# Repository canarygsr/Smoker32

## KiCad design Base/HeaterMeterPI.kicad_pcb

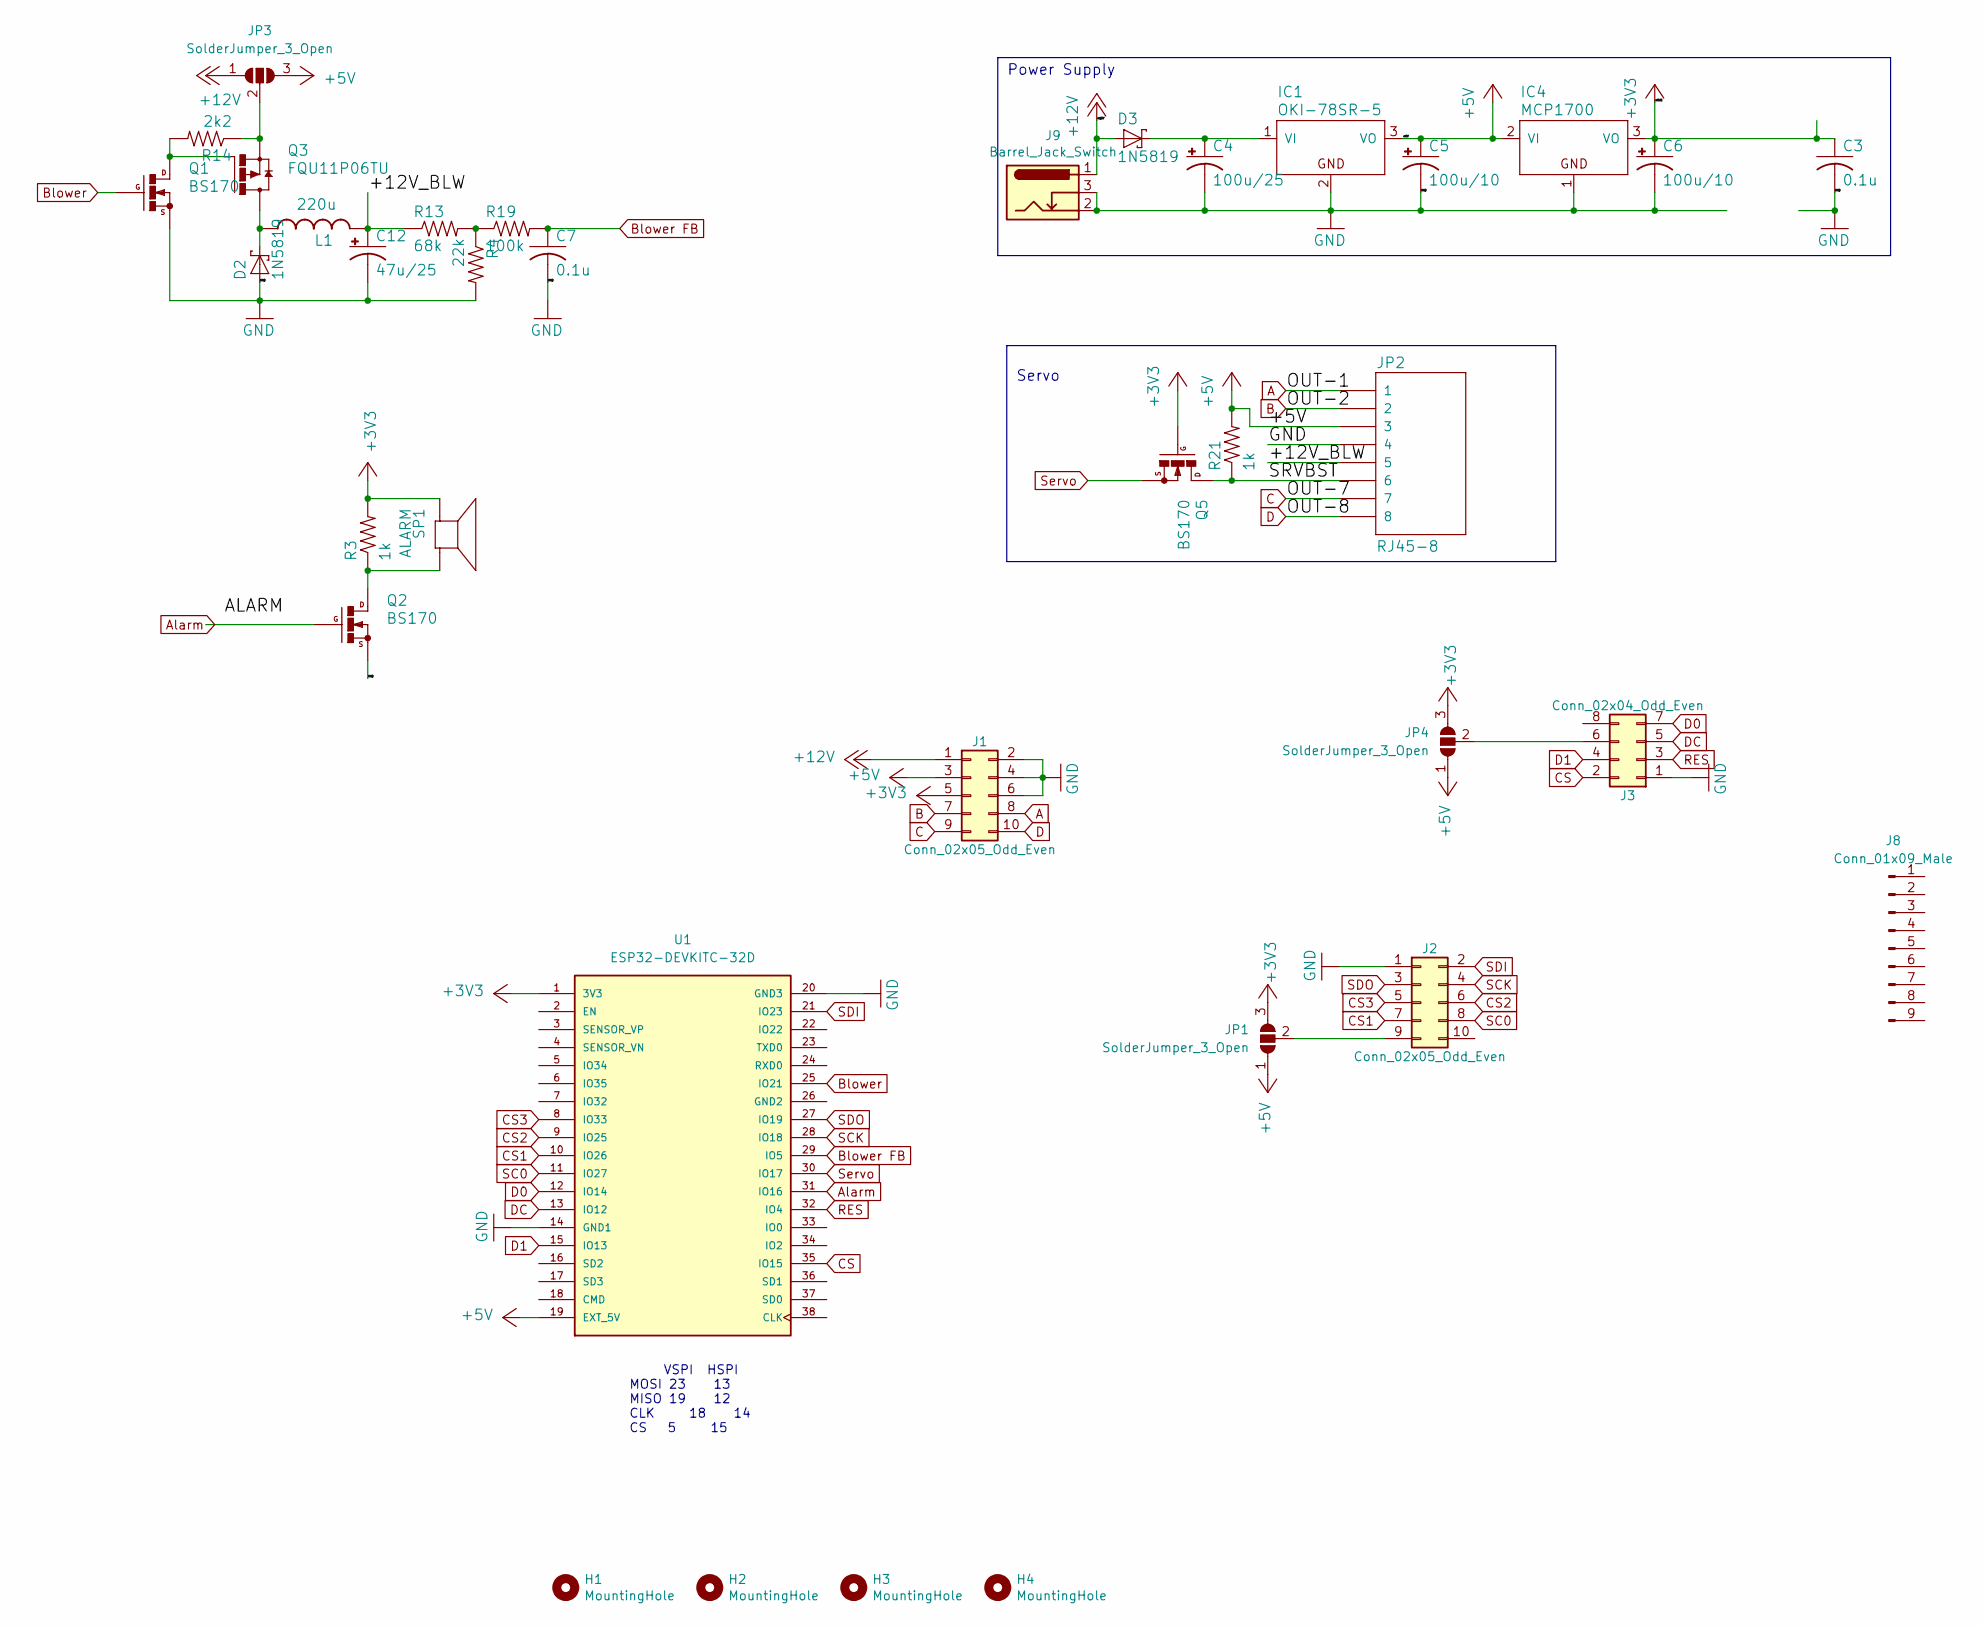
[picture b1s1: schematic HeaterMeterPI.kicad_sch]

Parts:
C3, C7: 0.1u; C025-025X050
C4: 100u/25; E2,5-6
C5, C6: 100u/10; E2,5-5
C12: 47u/25; E2,5-5
D2, D3: 1N5819; DO41-7
H1, H2, H3, H4: MountingHole; MountingHole_2.1mm
IC1: OKI-78SR-5; TO220HMURATA
IC4: MCP1700; TO92
J1: Conn_02x05_Odd_Even; PinHeader_2x06_P2.54mm_Vertical
J2: Conn_02x05_Odd_Even; PinHeader_1x09_P2.54mm_Vertical
J3: Conn_02x04_Odd_Even; PinHeader_1x07_P2.54mm_Vertical
J8: Conn_01x09_Male; Quad Max3186
J9: Barrel_Jack_Switch; BarrelJack_Horizontal
JP1, JP3, JP4: SolderJumper_3_Open; SolderJumper-3_P1.3mm_Open_RoundedPad1.0x1.5mm_NumberLabels
JP2: RJ45-8; RJ45-8-1H
L1: 220u; E5-9
Q1, Q2, Q5: BS170; SOT54E
Q3: FQU11P06TU; TO251
R3, R21: 1k; 0204_7
R4: 22k; 0204_7
R13: 68k; 0204_7
R14: 2k2; 0204_7
R19: 100k; 0204_7
SP1: ALARM; AL11P
U1: ESP32-DEVKITC-32D; MODULE_ESP32-NodeMCU; PARTREV 4

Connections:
+3V3: C3.1, C6.+, IC4.3 (VO), J1.5, JP1.3 (B), JP4.3 (B), Q5.G, R3.2, SP1.+, U1.1 (3V3)
+5V: C5.+, IC1.3 (VO), IC4.2 (VI), J1.3, JP1.1 (A), JP2.3, JP3.3 (B), JP4.1 (A), R21.2, U1.19 (EXT_5V)
+12V: D3.A, J1.1, J9.1, JP3.1 (A)
/+12V_BLW: C12.+, JP2.5, L1.NEG (2), R13.1
/SRVBST: JP2.6, Q5.D, R21.1
A: J1.8, JP2.1
Alarm: Q2.G, U1.31 (IO16)
B: J1.7, JP2.2
Blower: Q1.G, U1.25 (IO21)
Blower FB: C7.1, R19.2, U1.29 (IO5)
C: J1.9, JP2.7
CS: J3.2, U1.35 (IO15)
CS1: J2.7, U1.10 (IO26)
CS2: J2.6, U1.9 (IO25)
CS3: J2.5, U1.8 (IO33)
D: J1.10, JP2.8
D0: J3.7, U1.12 (IO14)
D1: J3.4, U1.15 (IO13)
DC: J3.5, U1.13 (IO12)
GND: C3.2, C4.-, C5.-, C6.-, C7.2, C12.-, D2.A, IC1.2 (GND), IC4.1 (GND), J1.2, J1.4, J1.6, J2.1, J3.1, J9.2, J9.3, JP2.4, Q1.S, Q2.S, R4.2, U1.14 (GND1), U1.20 (GND3)
unnamed: C4.+, D3.C, IC1.1 (VI)
unnamed: D2.C, L1.POS (1), Q3.2@1 (D), Q3.2@2 (D)
unnamed: J2.9, JP1.2 (C)
unnamed: J3.6, JP4.2 (C)
unnamed: JP3.2 (C), Q3.3 (S), R14.1
unnamed: Q1.D, Q3.1 (G), R14.2
unnamed: Q2.D, R3.1, SP1.-
unnamed: R4.1, R13.2, R19.1
RES: J3.3, U1.32 (IO4)
SC0: J2.8, U1.11 (IO27)
SCK: J2.4, U1.28 (IO18)
SDI: J2.2, U1.21 (IO23)
SDO: J2.3, U1.27 (IO19)
Servo: Q5.S, U1.30 (IO17)

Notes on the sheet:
Power Supply
Servo
VSPI HSPI MOSI 23 13 MISO 19 12 CLK 18 14 CS 5 15

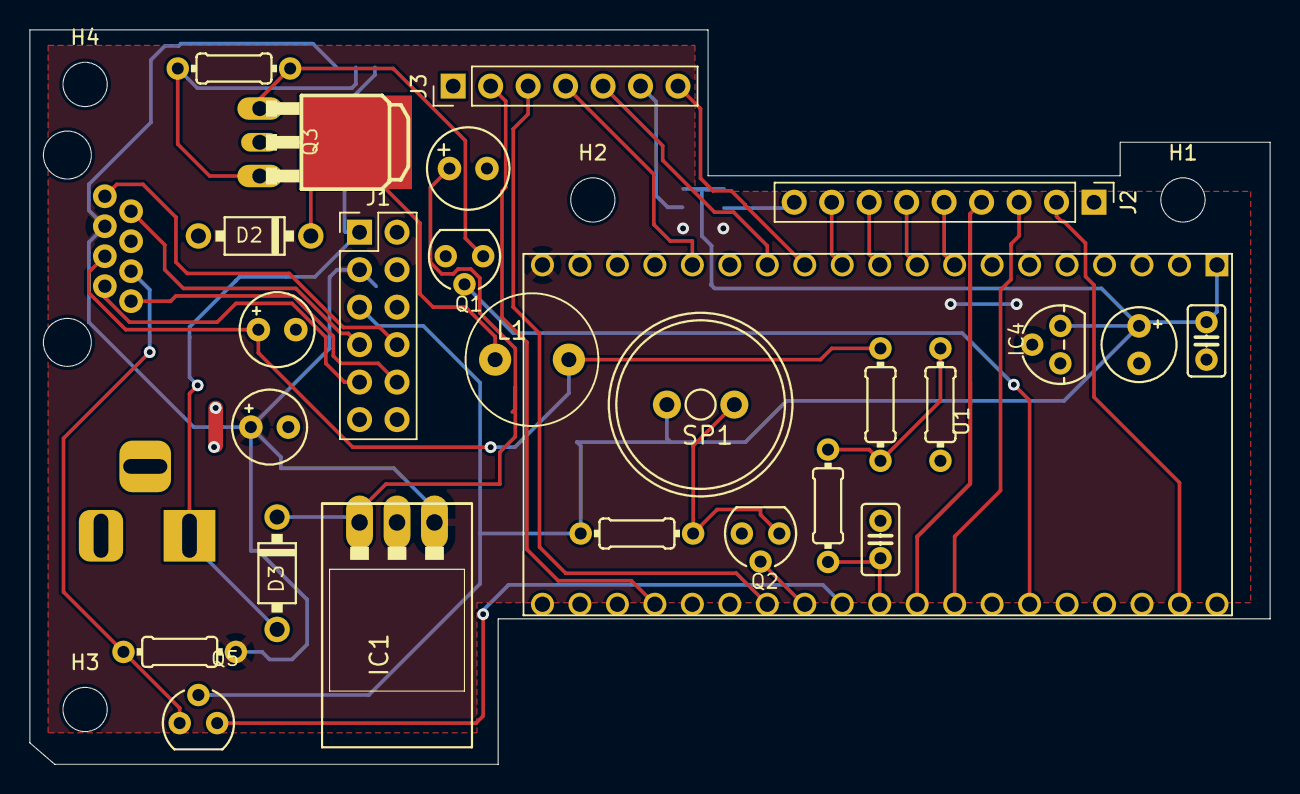
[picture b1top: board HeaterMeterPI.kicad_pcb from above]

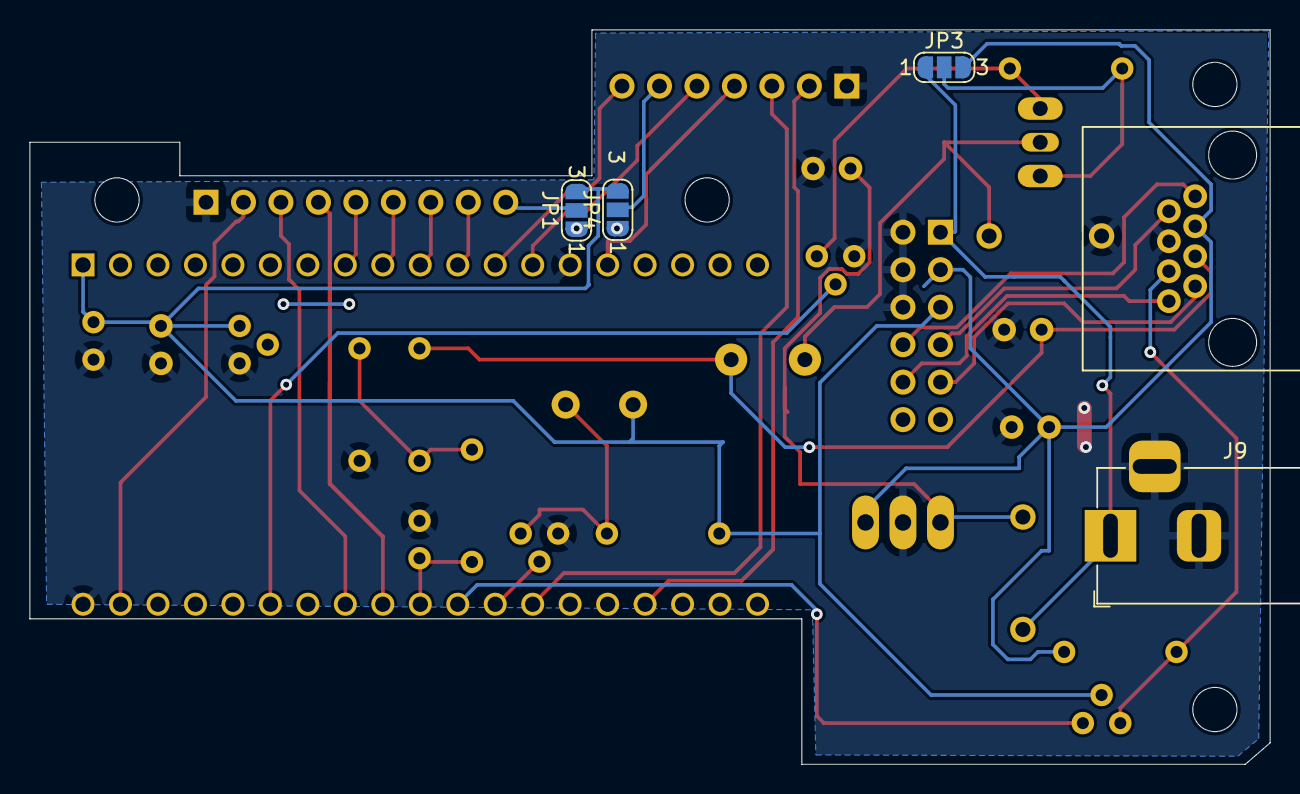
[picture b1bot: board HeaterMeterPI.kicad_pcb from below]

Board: 2 copper layers, 84.1 x 49.8 mm, 35 parts (5 on the bottom side), 34 nets.

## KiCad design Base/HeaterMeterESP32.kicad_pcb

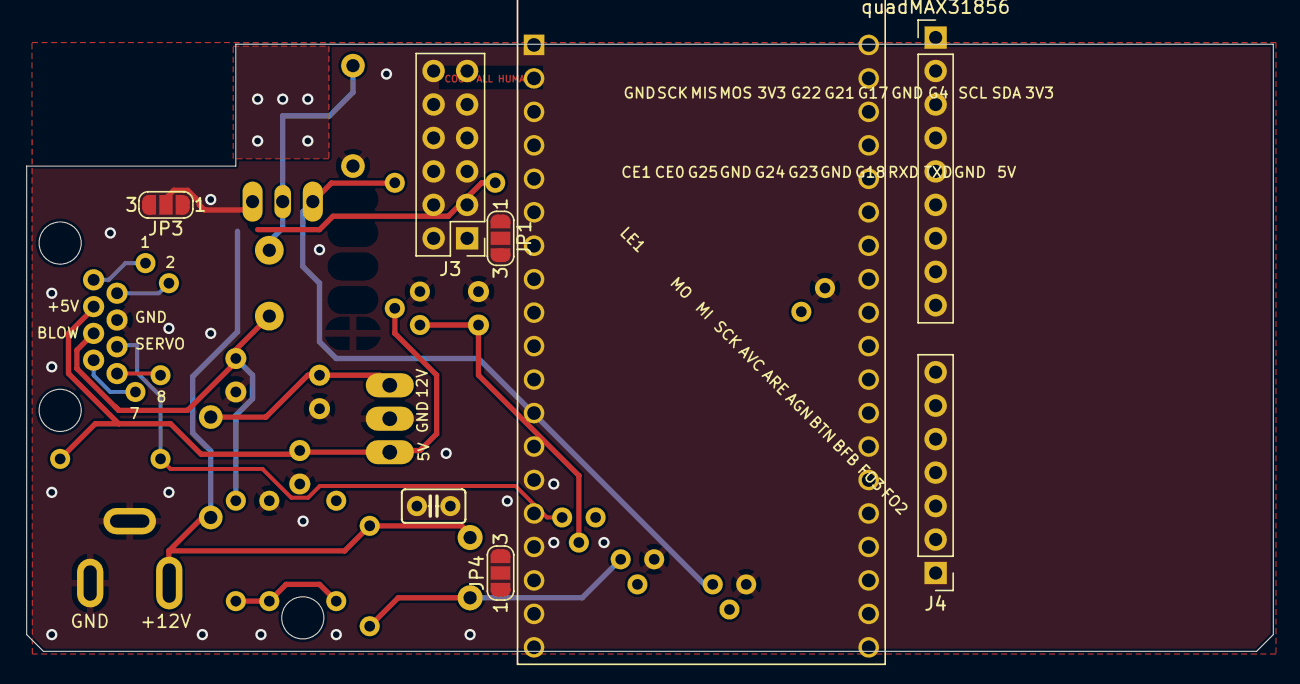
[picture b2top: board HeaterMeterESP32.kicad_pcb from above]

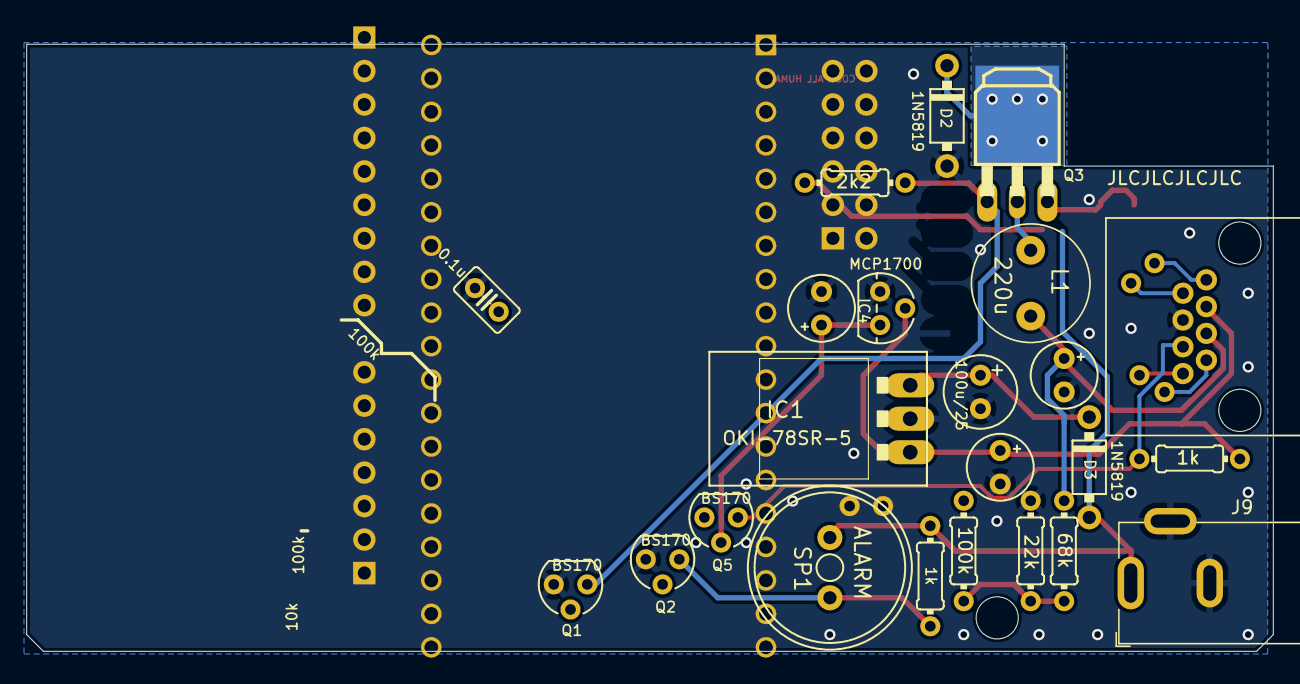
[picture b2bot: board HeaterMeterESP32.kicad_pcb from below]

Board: 2 copper layers, 94.6 x 46.1 mm, 37 parts (23 on the bottom side), 33 nets.

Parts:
C3, C7: 0.1u; C025-025X050
C4: 100u/25; E2,5-6
C5, C6: 100u/10; E2,5-5
C12: 47u/25; E2,5-5
D2, D3: 1N5819; DO41-7
H1, H2: MountingHole; MountingHole_3.2mm_M3_ISO14580
IC1: OKI-78SR-5; TO220HMURATA
IC4: MCP1700; TO92
J3: Conn_02x03_Odd_Even; PinHeader_2x06_P2.54mm_Vertical
J4: 0.96'OLED; PinHeader_1x07_P2.54mm_Vertical
J9: Barrel_Jack_Switch; BarrelJack_Horizontal
JP1, JP3, JP4: SolderJumper_3_Open; SolderJumper-3_P1.3mm_Open_RoundedPad1.0x1.5mm_NumberLabels
JP2: RJ45-8; RJ45-8-1H
L1: 220u; E5-9
Q1, Q2, Q5: BS170; SOT54E
Q3: FQU11P06TU; TO251
R3, R21: 1k; 0204_7
R4: 22k; 0204_7
R13: 68k; 0204_7
R14: 2k2; 0204_7
R19: 100k; 0204_7
SP1: ALARM; AL11P
U1: ESP32-DEVKITC-32D; MODULE_ESP32-DEVKITC-32D
U$1, U$2, U$3, U$4: THROUGH-HOLE; PAD-032
quadMAX31856: Conn_01x09; PinHeader_1x09_P2.54mm_Vertical

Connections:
+3V3: C3.1, C6.+, IC4.3 (VO), J3.5, JP1.3 (B), Q5.G, U1.1 (3V3)
+5V: C5.+, IC1.3 (VO), IC4.2 (VI), J3.3, JP1.1 (A), JP2.3, JP3.3 (B), JP4.3 (B), R21.2, U1.19 (EXT_5V)
+12V: D3.A, J3.1, J9.1, JP3.1 (A), JP4.1 (A)
/+12V_BLW: C12.+, JP2.5, L1.NEG (2), R13.1
/OUT-1: JP2.1, U$3.P
/OUT-2: JP2.2, U$4.P
/OUT-7: JP2.7, U$2.P
/OUT-8: JP2.8, U$1.P
/SRVBST: JP2.6, Q5.D, R21.1
Alarm: Q2.G, U1.31 (IO16)
Blower FB: C7.1, R19.2, U1.29 (IO5)
CS: J4.1, U1.35 (IO15)
CS1: U1.10 (IO26), quadMAX31856.6
CS2: U1.9 (IO25), quadMAX31856.5
CS3: U1.8 (IO33), quadMAX31856.4
D0: J4.5, U1.12 (IO14)
D1: J4.4, U1.15 (IO13)
DC: J4.2, U1.13 (IO12)
GND: C3.2, C4.-, C5.-, C6.-, C7.2, C12.-, D2.A, IC1.2 (GND), IC4.1 (GND), J3.2, J3.4, J3.6, J4.7, J9.2, J9.3, JP2.4, Q1.S, Q2.S, R4.2, U1.14 (GND1), U1.20 (GND3), quadMAX31856.1
unnamed: C4.+, D3.C, IC1.1 (VI)
unnamed: D2.C, L1.POS (1), Q3.2@1 (D), Q3.2@2 (D)
unnamed: JP1.2 (C), quadMAX31856.9
unnamed: JP3.2 (C), Q3.3 (S), R14.1
unnamed: JP4.2 (C), R3.2, SP1.+
unnamed: Q1.D, Q3.1 (G), R14.2
unnamed: Q2.D, R3.1, SP1.-
unnamed: R4.1, R13.2, R19.1
RES: J4.3, U1.32 (IO4)
SC0: U1.11 (IO27), quadMAX31856.7
SCK: U1.28 (IO18), quadMAX31856.2
SDI: U1.21 (IO23), quadMAX31856.3
SDO: U1.27 (IO19), quadMAX31856.8
Servo: Q5.S, U1.30 (IO17)

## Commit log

2022-04-14 ESP32 Interface board with QuadMax temp sensors
    ESP32 smoker
2022-04-14 ESP32 Quadmax smoker temp sensor
    aaaaaaaaa
2022-05-03 Update Quad_MAX31856.h
    updated pins for rev a of board
2023-01-09 V2
    Updated trial working beta from ESP8266
    Changes to Files system to support ESP32
    Also updated to ue the sample webserver.h
